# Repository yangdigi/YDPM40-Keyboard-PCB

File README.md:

# YDPM40 Keyboard PCB
My very first keyboard PCB when I was a newbie. Its controller is atmega328p.

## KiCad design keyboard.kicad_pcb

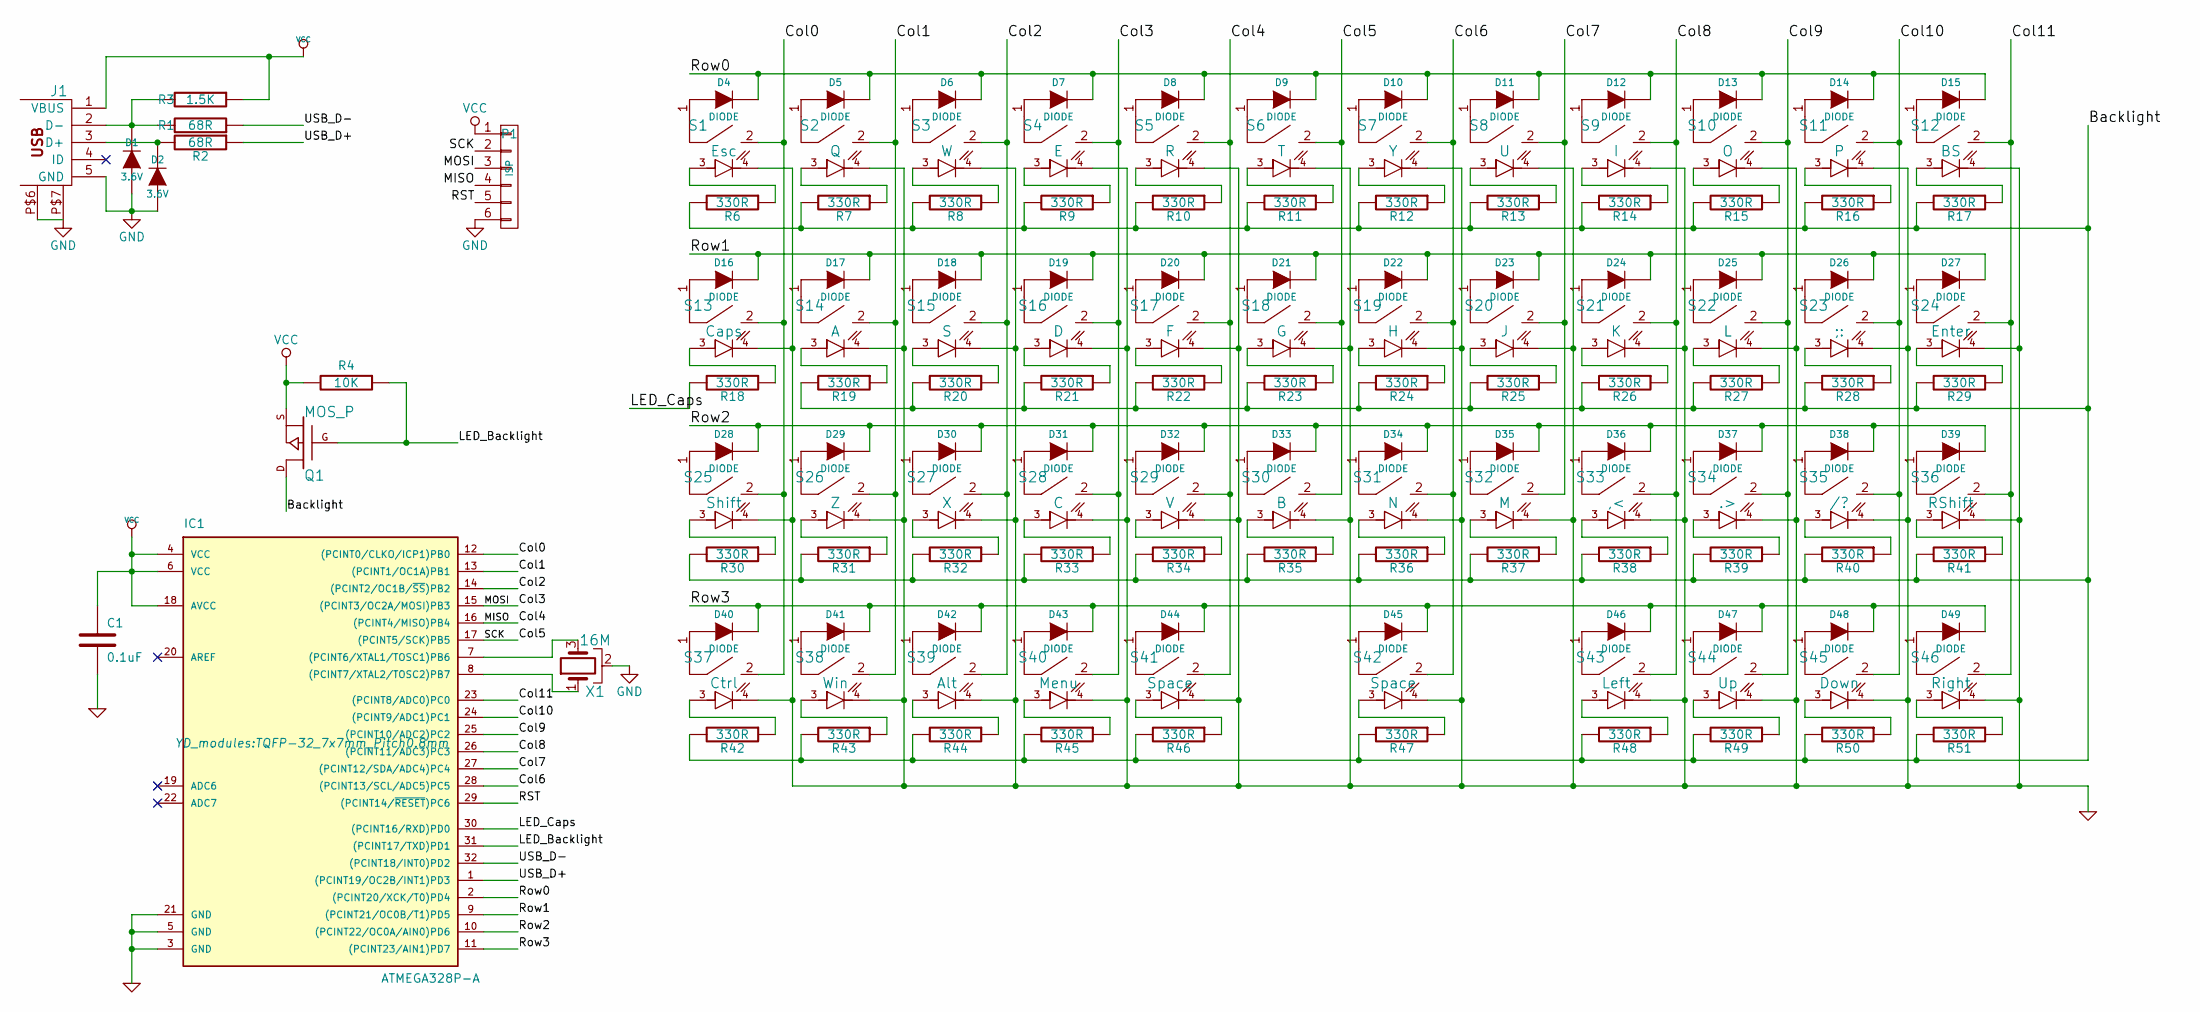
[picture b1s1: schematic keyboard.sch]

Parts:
C1: 0.1uF; C_0805
D1, D2: 3.6V; D_0805
D4, D5, D6, D7, D8, D9, D10, D11, D12, D13, D14, D15, D16, D17, D18, D19, D20, D21, D22, D23, D24, D25, D26, D27, D28, D29, D30, D31, D32, D33, D34, D35, D36, D37, D38, D39, D40, D41, D42, D43, D44, D45, D46, D47, D48, D49: DIODE; D_0805
IC1: ATMEGA328P-A; TQFP-32_7x7mm_Pitch0.8mm
J1: USBMINI_B05; DX_USB
P1: ISP; ISP_1x6_1.27mm
Q1: MOS_P; SOT-23
R1, R2: 68R; R_0805
R3: 1.5K; R_0805
R4: 10K; R_0805
R6, R7, R8, R9, R10, R11, R12, R13, R14, R15, R16, R17, R18, R19, R20, R21, R22, R23, R24, R25, R26, R27, R28, R29, R30, R31, R32, R33, R34, R35, R36, R37, R38, R39, R40, R41, R42, R43, R44, R45, R46, R47, R48, R49, R50, R51: 330R; R_0805
S1: Esc; MX1A_LED
S2: Q; MX1A_LED
S3: W; MX1A_LED
S4: E; MX1A_LED
S5: R; MX1A_LED
S6: T; MX1A_LED
S7: Y; MX1A_LED
S8: U; MX1A_LED
S9: I; MX1A_LED
S10: O; MX1A_LED
S11: P; MX1A_LED
S12: BS; MX1A_LED
S13: Caps; MX1A_LED
S14: A; MX1A_LED
S15: S; MX1A_LED
S16: D; MX1A_LED
S17: F; MX1A_LED
S18: G; MX1A_LED
S19: H; MX1A_LED
S20: J; MX1A_LED
S21: K; MX1A_LED
S22: L; MX1A_LED
S23: ;:; MX1A_LED
S24: Enter; MX1A_LED
S25: Shift; MX1A_LED
S26: Z; MX1A_LED
S27: X; MX1A_LED
S28: C; MX1A_LED
S29: V; MX1A_LED
S30: B; MX1A_LED
S31: N; MX1A_LED
S32: M; MX1A_LED
S33: ,<; MX1A_LED
S34: .>; MX1A_LED
S35: /?; MX1A_LED
S36: RShift; MX1A_LED
S37: Ctrl; MX1A_LED
S38: Win; MX1A_LED
S39: Alt; MX1A_LED
S40: Menu; MX1A_LED
S41, S42: Space; MX1A_LED
S43: Left; MX1A_LED
S44: Up; MX1A_LED
S45: Down; MX1A_LED
S46: Right; MX1A_LED
X1: 16M; CSTCE

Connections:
/Backlight: Q1.D, R6.2, R7.2, R8.2, R9.2, R10.2, R11.2, R12.2, R13.2, R14.2, R15.2, R16.2, R17.2, R19.2, R20.2, R21.2, R22.2, R23.2, R24.2, R25.2, R26.2, R27.2, R28.2, R29.2, R30.2, R31.2, R32.2, R33.2, R34.2, R35.2, R36.2, R37.2, R38.2, R39.2, R40.2, R41.2, R42.2, R43.2, R44.2, R45.2, R46.2, R47.2, R48.2, R49.2, R50.2, R51.2
/Col0: IC1.12 ((PCINT0/CLKO/ICP1)PB0), S1.2, S13.2, S25.2, S37.2; also elsewhere on the board
/Col1: IC1.13 ((PCINT1/OC1A)PB1), S2.2, S14.2, S26.2, S38.2; also elsewhere on the board
/Col2: IC1.14 ((PCINT2/OC1B/~SS~)PB2), S3.2, S15.2, S27.2, S39.2; also elsewhere on the board
/Col3: IC1.15 ((PCINT3/OC2A/MOSI)PB3), P1.3, S4.2, S16.2, S28.2, S40.2; also elsewhere on the board
/Col4: IC1.16 ((PCINT4/MISO)PB4), P1.4, S5.2, S17.2, S29.2, S41.2; also elsewhere on the board
/Col5: IC1.17 ((PCINT5/SCK)PB5), P1.2, S6.2, S18.2, S30.2; also elsewhere on the board
/Col6: IC1.28 ((PCINT13/SCL/ADC5)PC5), S7.2, S19.2, S31.2, S42.2; also elsewhere on the board
/Col7: IC1.27 ((PCINT12/SDA/ADC4)PC4), S8.2, S20.2, S32.2; also elsewhere on the board
/Col8: IC1.26 ((PCINT11/ADC3)PC3), S9.2, S21.2, S33.2, S43.2; also elsewhere on the board
/Col9: IC1.25 ((PCINT10/ADC2)PC2), S10.2, S22.2, S34.2, S44.2; also elsewhere on the board
/Col10: IC1.24 ((PCINT9/ADC1)PC1), S11.2, S23.2, S35.2, S45.2
/Col11: IC1.23 ((PCINT8/ADC0)PC0), S12.2, S24.2, S36.2, S46.2; also elsewhere on the board
/LED_Backlight: IC1.31 ((PCINT17/TXD)PD1), Q1.G, R4.1
/LED_Caps: IC1.30 ((PCINT16/RXD)PD0), R18.2
/RST: IC1.29 ((PCINT14/~RESET~)PC6), P1.5
/Row0: D4.2 (K), D5.2 (K), D6.2 (K), D7.2 (K), D8.2 (K), D9.2 (K), D10.2 (K), D11.2 (K), D12.2 (K), D13.2 (K), D14.2 (K), D15.2 (K), IC1.2 ((PCINT20/XCK/T0)PD4)
/Row1: D16.2 (K), D17.2 (K), D18.2 (K), D19.2 (K), D20.2 (K), D21.2 (K), D22.2 (K), D23.2 (K), D24.2 (K), D25.2 (K), D26.2 (K), D27.2 (K), IC1.9 ((PCINT21/OC0B/T1)PD5)
/Row2: D28.2 (K), D29.2 (K), D30.2 (K), D31.2 (K), D32.2 (K), D33.2 (K), D34.2 (K), D35.2 (K), D36.2 (K), D37.2 (K), D38.2 (K), D39.2 (K), IC1.10 ((PCINT22/OC0A/AIN0)PD6)
/Row3: D40.2 (K), D41.2 (K), D42.2 (K), D43.2 (K), D44.2 (K), D45.2 (K), D46.2 (K), D47.2 (K), D48.2 (K), D49.2 (K), IC1.11 ((PCINT23/AIN1)PD7)
/USB_D+: IC1.1 ((PCINT19/OC2B/INT1)PD3), R2.1
/USB_D-: IC1.32 ((PCINT18/INT0)PD2), R1.1
GND: C1.2, D1.1 (A), D2.1 (A), IC1.3 (GND), IC1.5 (GND), IC1.21 (GND), J1.5 (GND), J1.P$6, J1.P$7, P1.6, S1.4, S2.4, S3.4, S4.4, S5.4, S6.4, S7.4, S8.4, S9.4, S10.4, S11.4, S12.4, S13.4, S14.4, S15.4, S16.4, S17.4, S18.4, S19.4, S20.4, S21.4, S22.4, S23.4, S24.4, S25.4, S26.4, S27.4, S28.4, S29.4, S30.4, S31.4, S32.4, S33.4, S34.4, S35.4, S36.4, S37.4, S38.4, S39.4, S40.4, S41.4, S42.4, S43.4, S44.4, S45.4, S46.4, X1.2; also elsewhere on the board
unnamed: D1.2 (K), J1.2 (D-), R1.2, R3.2
unnamed: D2.2 (K), J1.3 (D+), R2.2
unnamed: D4.1 (A), S1.1
unnamed: D5.1 (A), S2.1
unnamed: D6.1 (A), S3.1
unnamed: D7.1 (A), S4.1
unnamed: D8.1 (A), S5.1
unnamed: D9.1 (A), S6.1
unnamed: D10.1 (A), S7.1
unnamed: D11.1 (A), S8.1
unnamed: D12.1 (A), S9.1
unnamed: D13.1 (A), S10.1
unnamed: D14.1 (A), S11.1
unnamed: D15.1 (A), S12.1
unnamed 37: D16.1 (A), S13.1; also elsewhere on the board
unnamed 38: D17.1 (A), S14.1; also elsewhere on the board
unnamed 39: D18.1 (A), S15.1; also elsewhere on the board
unnamed 40: D19.1 (A), S16.1; also elsewhere on the board
unnamed 41: D20.1 (A), S17.1; also elsewhere on the board
unnamed 42: D21.1 (A), S18.1; also elsewhere on the board
unnamed 43: D22.1 (A), S19.1; also elsewhere on the board
unnamed 44: D23.1 (A), S20.1; also elsewhere on the board
unnamed 45: D24.1 (A), S21.1; also elsewhere on the board
unnamed 46: D25.1 (A), S22.1; also elsewhere on the board
unnamed: D26.1 (A), S23.1
unnamed 48: D27.1 (A), S24.1; also elsewhere on the board
unnamed: D28.1 (A), S25.1
unnamed: D29.1 (A), S26.1
unnamed: D30.1 (A), S27.1
unnamed: D31.1 (A), S28.1
unnamed: D32.1 (A), S29.1
unnamed: D33.1 (A), S30.1
unnamed: D34.1 (A), S31.1
unnamed: D35.1 (A), S32.1
unnamed: D36.1 (A), S33.1
unnamed: D37.1 (A), S34.1
unnamed: D38.1 (A), S35.1
unnamed: D39.1 (A), S36.1
unnamed: D40.1 (A), S37.1
unnamed: D41.1 (A), S38.1
unnamed: D42.1 (A), S39.1
unnamed 64: D43.1 (A), S40.1; also elsewhere on the board
unnamed 65: D44.1 (A), S41.1; also elsewhere on the board
unnamed 66: D45.1 (A), S42.1; also elsewhere on the board
unnamed 67: D46.1 (A), S43.1; also elsewhere on the board
unnamed: D47.1 (A), S44.1
unnamed: D48.1 (A), S45.1
unnamed: D49.1 (A), S46.1
unnamed: IC1.7 ((PCINT6/XTAL1/TOSC1)PB6), X1.3
unnamed: IC1.8 ((PCINT7/XTAL2/TOSC2)PB7), X1.1
unnamed: R6.1, S1.3
unnamed: R7.1, S2.3
unnamed: R8.1, S3.3
unnamed: R9.1, S4.3
unnamed: R10.1, S5.3
unnamed: R11.1, S6.3
unnamed: R12.1, S7.3
unnamed: R13.1, S8.3
unnamed: R14.1, S9.3
unnamed: R15.1, S10.3
unnamed: R16.1, S11.3
unnamed: R17.1, S12.3
unnamed 85: R18.1, S13.3; also elsewhere on the board
unnamed 86: R19.1, S14.3; also elsewhere on the board
unnamed 87: R20.1, S15.3; also elsewhere on the board
unnamed 88: R21.1, S16.3; also elsewhere on the board
unnamed 89: R22.1, S17.3; also elsewhere on the board
unnamed 90: R23.1, S18.3; also elsewhere on the board
unnamed 91: R24.1, S19.3; also elsewhere on the board
unnamed 92: R25.1, S20.3; also elsewhere on the board
unnamed 93: R26.1, S21.3; also elsewhere on the board
unnamed 94: R27.1, S22.3; also elsewhere on the board
unnamed: R28.1, S23.3
unnamed 96: R29.1, S24.3; also elsewhere on the board
unnamed: R30.1, S25.3
unnamed: R31.1, S26.3
unnamed: R32.1, S27.3
unnamed: R33.1, S28.3
unnamed: R34.1, S29.3
unnamed: R35.1, S30.3
unnamed: R36.1, S31.3
unnamed: R37.1, S32.3
unnamed: R38.1, S33.3
unnamed: R39.1, S34.3
unnamed: R40.1, S35.3
unnamed: R41.1, S36.3
unnamed: R42.1, S37.3
unnamed: R43.1, S38.3
unnamed: R44.1, S39.3
unnamed 112: R45.1, S40.3; also elsewhere on the board
unnamed 113: R46.1, S41.3; also elsewhere on the board
unnamed 114: R47.1, S42.3; also elsewhere on the board
unnamed 115: R48.1, S43.3; also elsewhere on the board
unnamed: R49.1, S44.3
unnamed: R50.1, S45.3
unnamed: R51.1, S46.3
VCC: C1.1, IC1.4 (VCC), IC1.6 (VCC), IC1.18 (AVCC), J1.1 (VBUS), P1.1, Q1.S, R3.1, R4.2

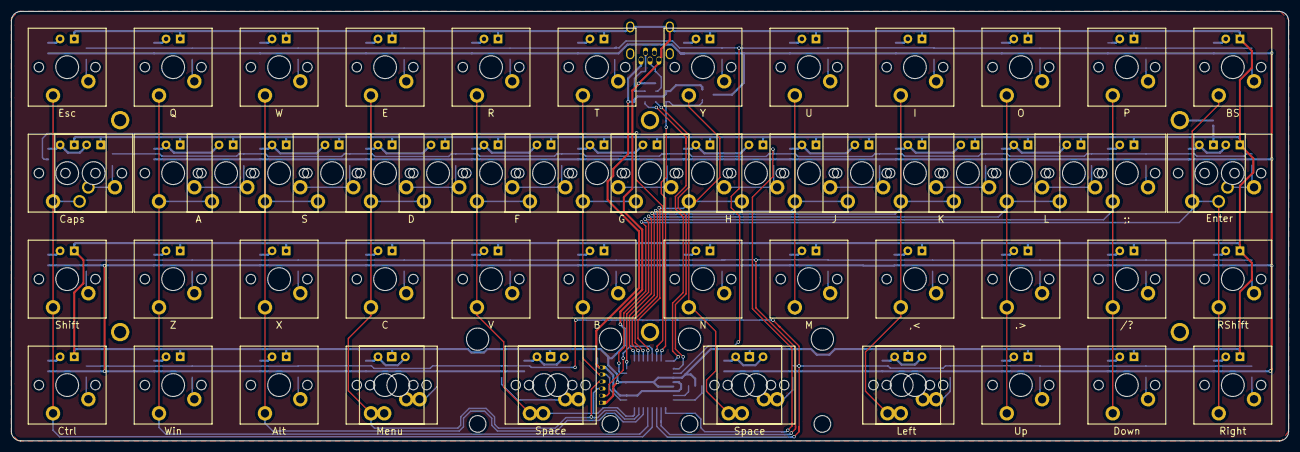
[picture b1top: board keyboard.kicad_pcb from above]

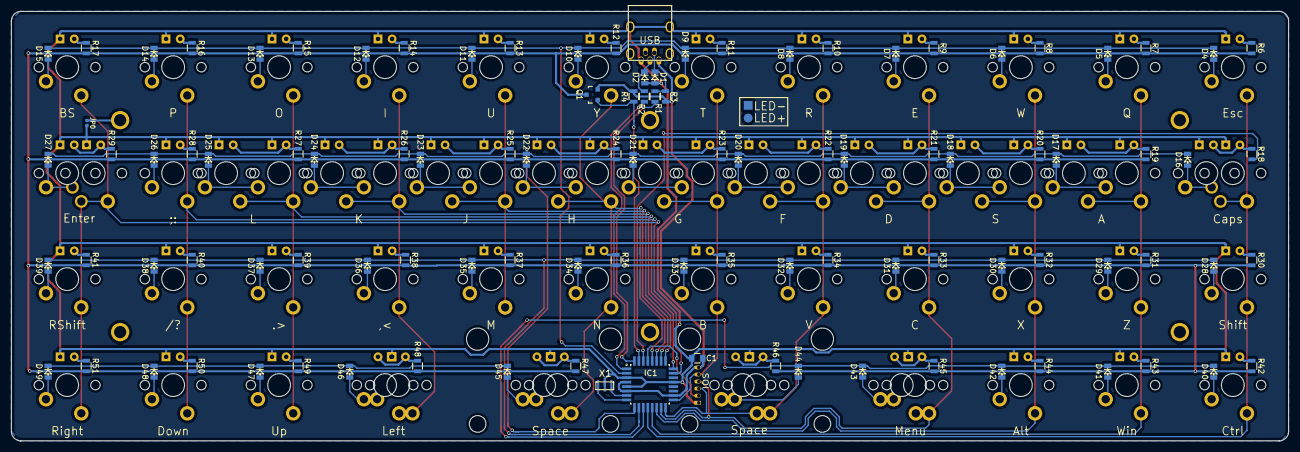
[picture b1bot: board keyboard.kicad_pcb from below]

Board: 2 copper layers, 229.6 x 77.2 mm, 168 parts (106 on the bottom side), 120 nets.

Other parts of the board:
JP0: JP; R_0402_NoSilk
P1#2, P1#3: Pad; Pad_r1.0
S13#2: Caps; MX1A_LED
S14#2: A; MX1A_LED
S15#2: S; MX1A_LED
S16#2: D; MX1A_LED
S17#2: F; MX1A_LED
S18#2: G; MX1A_LED
S19#2: H; MX1A_LED
S20#2: J; MX1A_LED
S21#2: K; MX1A_LED
S22#2: L; MX1A_LED
S24#2: Enter; MX1A_LED
S40#2: Menu; MX1A_LED
S41#2, S42#2: Space; MX1A_LED
S43#2: Left; MX1A_LED

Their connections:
/Col0: S13#2.2; also elsewhere on the board
/Col1: S14#2.2; also elsewhere on the board
/Col2: S15#2.2; also elsewhere on the board
/Col3: S16#2.2, S40#2.2; also elsewhere on the board
/Col4: S17#2.2, S41#2.2; also elsewhere on the board
/Col5: S18#2.2; also elsewhere on the board
/Col6: S19#2.2, S42#2.2; also elsewhere on the board
/Col7: S20#2.2; also elsewhere on the board
/Col8: S21#2.2, S43#2.2; also elsewhere on the board
/Col9: S22#2.2; also elsewhere on the board
/Col11: S24#2.2; also elsewhere on the board
GND: S13#2.4, S14#2.4, S15#2.4, S16#2.4, S17#2.4, S18#2.4, S19#2.4, S20#2.4, S21#2.4, S22#2.4, S24#2.4, S40#2.4, S41#2.4, S42#2.4, S43#2.4; also elsewhere on the board
unnamed 37: S13#2.1; also elsewhere on the board
unnamed 38: S14#2.1; also elsewhere on the board
unnamed 39: S15#2.1; also elsewhere on the board
unnamed 40: S16#2.1; also elsewhere on the board
unnamed 41: S17#2.1; also elsewhere on the board
unnamed 42: S18#2.1; also elsewhere on the board
unnamed 43: S19#2.1; also elsewhere on the board
unnamed 44: S20#2.1; also elsewhere on the board
unnamed 45: S21#2.1; also elsewhere on the board
unnamed 46: S22#2.1; also elsewhere on the board
unnamed 48: S24#2.1; also elsewhere on the board
unnamed 64: S40#2.1; also elsewhere on the board
unnamed 65: S41#2.1; also elsewhere on the board
unnamed 66: S42#2.1; also elsewhere on the board
unnamed 67: S43#2.1; also elsewhere on the board
unnamed 85: S13#2.3; also elsewhere on the board
unnamed 86: S14#2.3; also elsewhere on the board
unnamed 87: S15#2.3; also elsewhere on the board
unnamed 88: S16#2.3; also elsewhere on the board
unnamed 89: S17#2.3; also elsewhere on the board
unnamed 90: S18#2.3; also elsewhere on the board
unnamed 91: S19#2.3; also elsewhere on the board
unnamed 92: S20#2.3; also elsewhere on the board
unnamed 93: S21#2.3; also elsewhere on the board
unnamed 94: S22#2.3; also elsewhere on the board
unnamed 96: S24#2.3; also elsewhere on the board
unnamed 112: S40#2.3; also elsewhere on the board
unnamed 113: S41#2.3; also elsewhere on the board
unnamed 114: S42#2.3; also elsewhere on the board
unnamed 115: S43#2.3; also elsewhere on the board

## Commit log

2018-11-24 YDPM40 by YANG
